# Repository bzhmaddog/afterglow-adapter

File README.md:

# Afterglow I/O adapter

An adapter board which purpose is to re-map Inputs and/or Ouputs of an Afterglow board
Two x9 pins molex broken into to a Heighteen pins 5.08mm Bornier

BOM:
- PCB board
- 2x 3.93 Molex male connector
- 18pins (3x6pins or  6x3pins or 9x2pins etc...) Bornier

TODO :
- Add holes for attachment

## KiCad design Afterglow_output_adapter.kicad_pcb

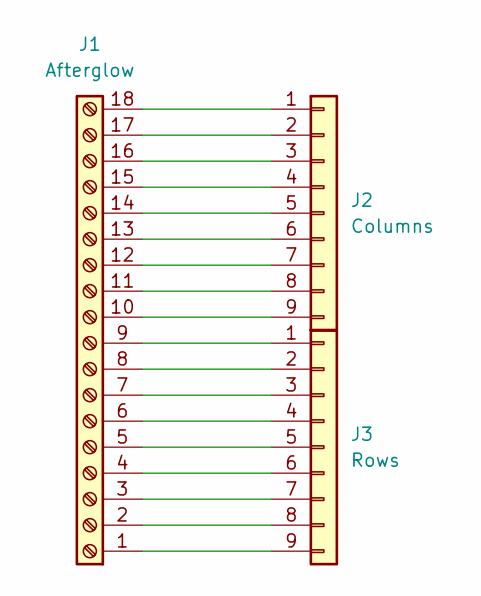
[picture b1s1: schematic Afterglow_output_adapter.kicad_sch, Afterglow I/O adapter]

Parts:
J1: Afterglow; TerminalBlock_bornier-18_P5.08mm
J2: Columns; Molex_KK-396_A-41791-0009_1x09_P3.96mm_Vertical
J3: Rows; Molex_KK-396_A-41791-0009_1x09_P3.96mm_Vertical

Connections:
unnamed: J1.1, J3.9
unnamed: J1.2, J3.8
unnamed: J1.3, J3.7
unnamed: J1.4, J3.6
unnamed: J1.5, J3.5
unnamed: J1.6, J3.4
unnamed: J1.7, J3.3
unnamed: J1.8, J3.2
unnamed: J1.9, J3.1
unnamed: J1.10, J2.9
unnamed: J1.11, J2.8
unnamed: J1.12, J2.7
unnamed: J1.13, J2.6
unnamed: J1.14, J2.5
unnamed: J1.15, J2.4
unnamed: J1.16, J2.3
unnamed: J1.17, J2.2
unnamed: J1.18, J2.1

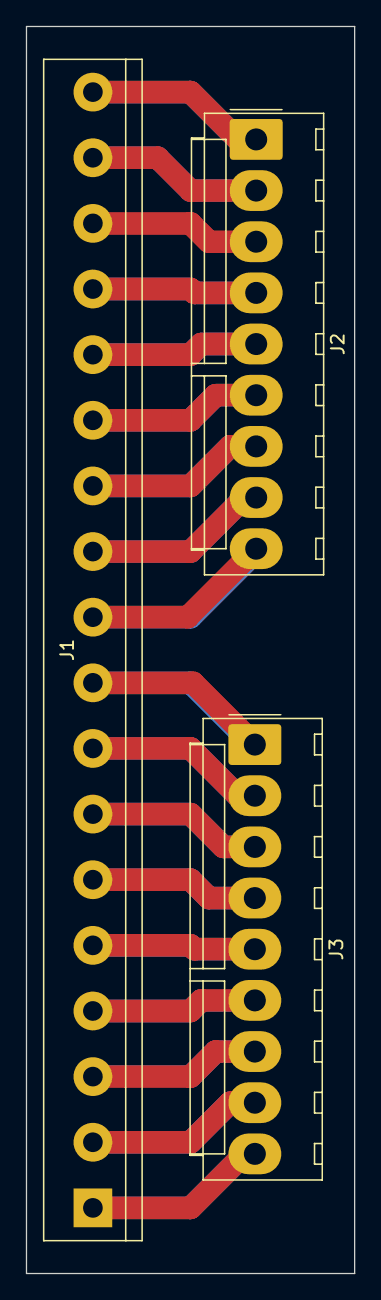
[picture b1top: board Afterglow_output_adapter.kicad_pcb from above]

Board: 2 copper layers, 25.4 x 96.5 mm, 3 parts (0 on the bottom side), 18 nets.

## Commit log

2024-02-17 Added PCB image in README.md
2024-03-09 Removed unwanted files and changed licence to CC NC
